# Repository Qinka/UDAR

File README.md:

# UDAR

This repo is a demo of **Ultrasound Detection And Ranging**, UDAR for short.
This demo includes a hardware design and a host software.
The hardware includes two servos, a ultrasound ranging module and FPGA IP core.
The host software will include the control program and other programs.

## Hardware

The hardware includes:

* 2-D holder
* Two servos for holder's x-axis and y-axis.
* Ultrasound ranging module(URM).
* ZigBee module(option)

The holder with two servos can change the direction of URM to $(x,y)$

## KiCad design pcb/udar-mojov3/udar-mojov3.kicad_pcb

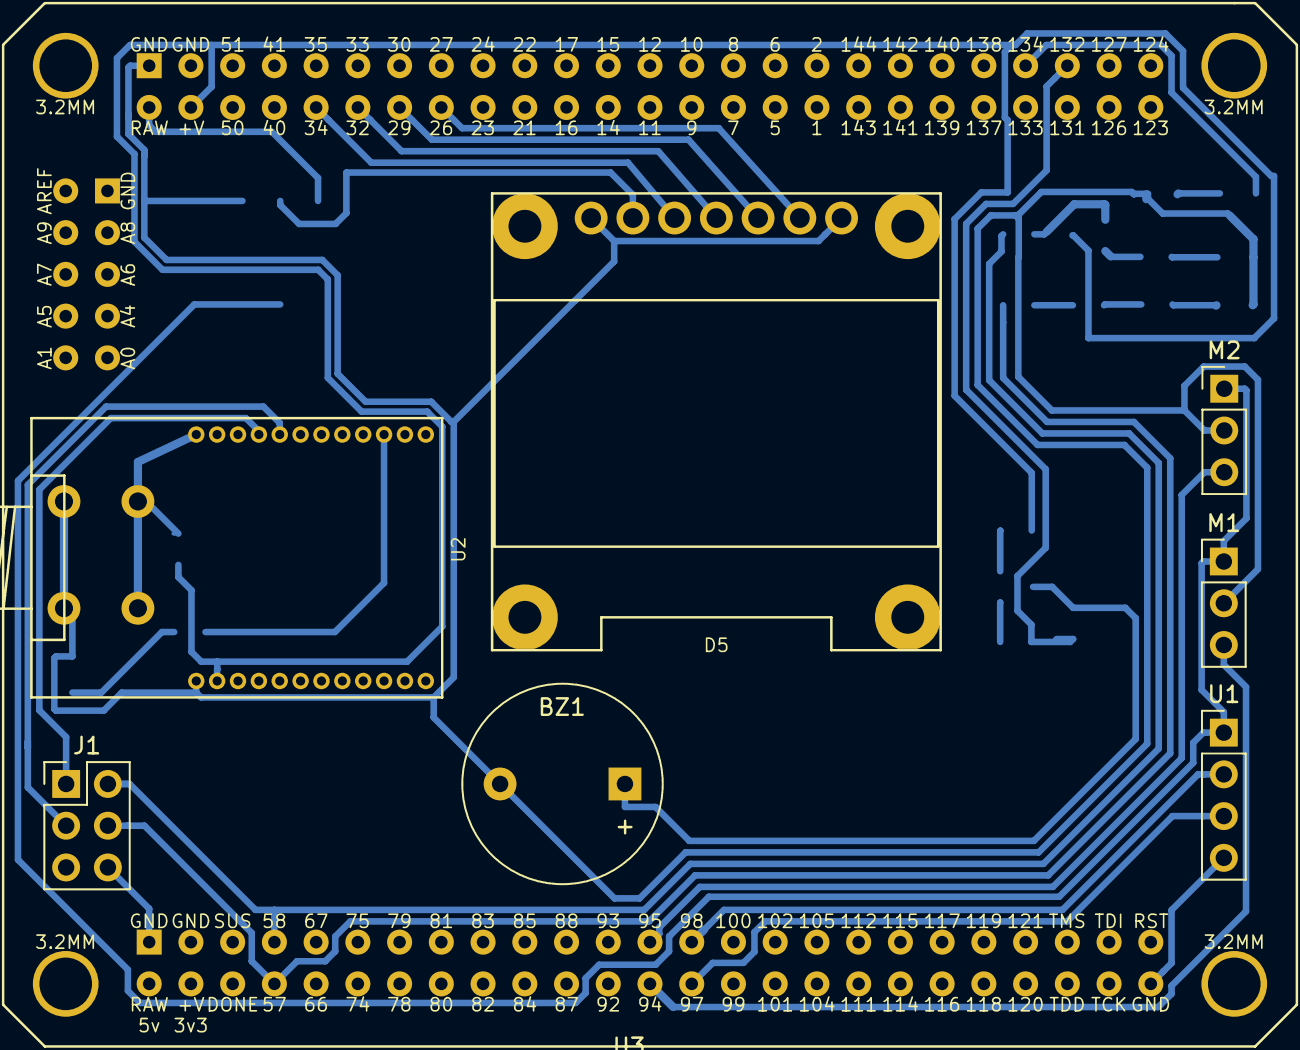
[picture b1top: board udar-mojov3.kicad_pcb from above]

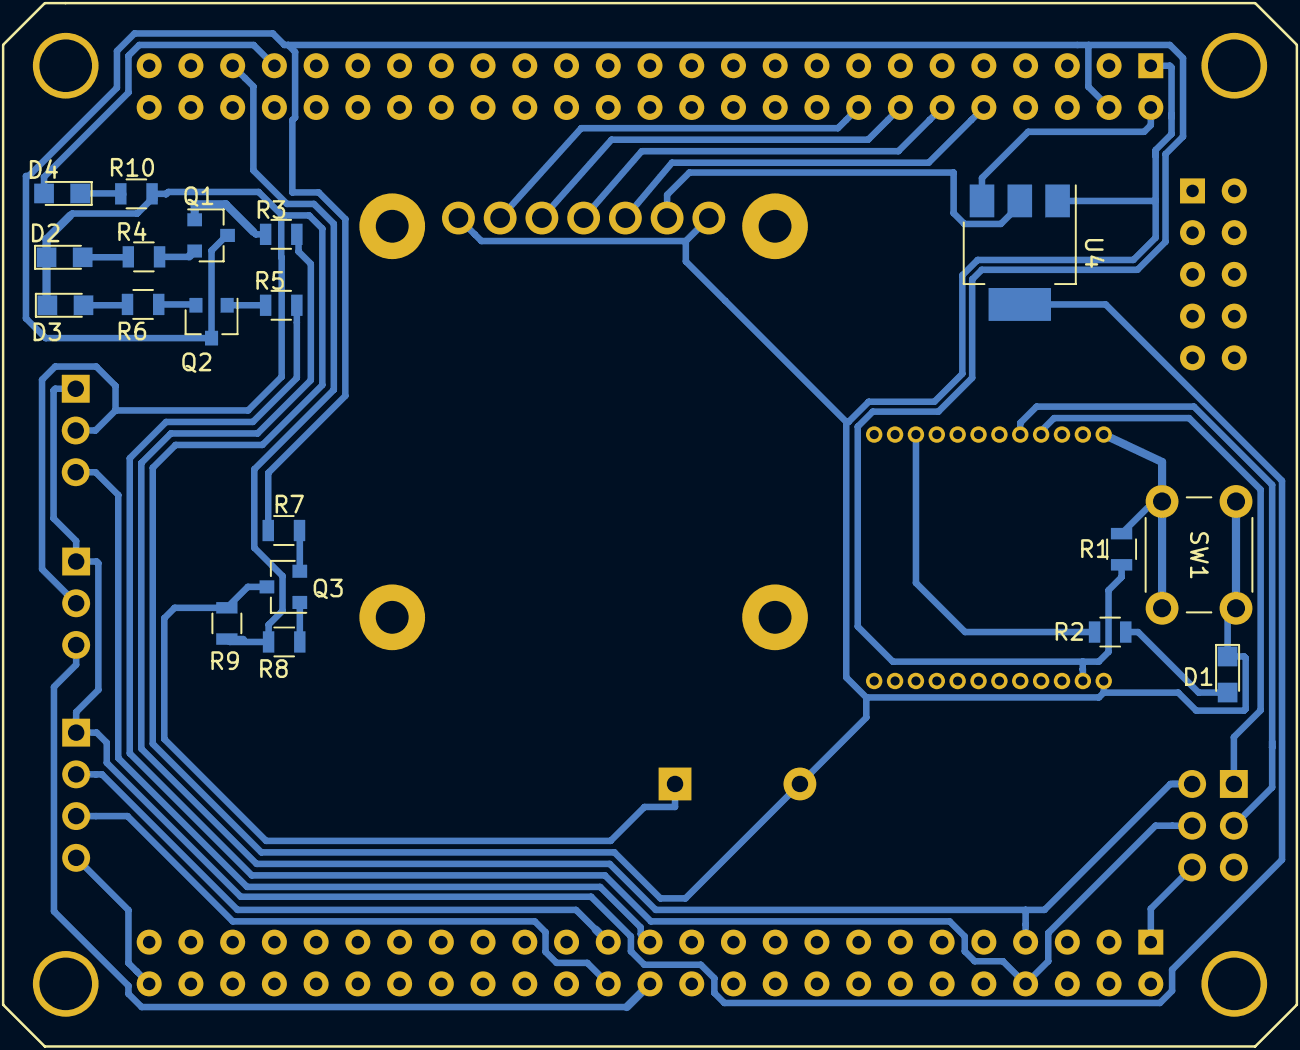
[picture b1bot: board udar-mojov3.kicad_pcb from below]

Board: 2 copper layers, 27 parts (19 on the bottom side), 31 nets.

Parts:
BZ1: Buzzer; Buzzer_12x9.5RM7.6
D1, D2, D3, D4: LED; LED_0805
D5: OLED; OLED_096_12864_SSD1306
J1: Conn_02x03_Odd_Even; Pin_Header_Straight_2x03_Pitch2.54mm
M1, M2: Motor_Servo_AirTronics; Pin_Header_Straight_1x03_Pitch2.54mm
Q1, Q2: Q_PNP_BCE; SOT-23
Q3: Q_NPN_BCE; SOT-23
R1, R2, R3, R4, R5, R6, R7, R8, R9, R10: R; R_0805
SW1: SW_Push; SW_PUSH_6mm
U1: HC-SR04; Pin_Header_Straight_1x04_Pitch2.54mm
U2: ZG-Mxx; ZG-Mxx_DIP_E
U3: Mojov3; mojov3
U4: AP1117-50; SOT-223-3_TabPin2

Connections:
+3V3: Q1.3, Q2.3, R1.1, R7.1, U2.A2, U3.+V
+5V: D5.2, M1.1, M2.1, U1.1, U4.2
/0.96 OLED/CLK: D5.3, U3.34
/0.96 OLED/DATA: D5.4, U3.32
/0.96 OLED/DC: D5.6, U3.26
/0.96 OLED/RST: D5.5, U3.29
/UART/UART_RX: J1.4, R5.2, U3.57
/UART/UART_TX: J1.2, R3.2, U3.58
/UDAR-board/Echo: U1.3, U3.97
/UDAR-board/PWM1: M1.3, U3.94
/UDAR-board/PWM2: M2.3, U3.95
/UDAR-board/Trig: U1.2, U3.98
GND: BZ1.2, D1.1, D2.1, D3.1, D5.1, D5.7, J1.6, M1.2, M2.2, R10.2, SW1.2, U1.4, U2.A1, U3.GND, U4.1
unnamed: BZ1.1, Q3.3, R9.2
unnamed: D1.2, R2.1
unnamed: D2.2, R4.2
unnamed: D3.2, R6.2
unnamed: D4.1, R10.1
unnamed: D4.2, U3.134
unnamed: J1.1, U2.B4
unnamed: J1.3, U2.B5
unnamed: Q1.1, R3.1
unnamed: Q1.2, R4.1
unnamed: Q2.1, R5.1
unnamed: Q2.2, R6.1
unnamed: Q3.1, R8.2
unnamed: Q3.2, R7.2
unnamed: R1.2, SW1.1, U2.B1
unnamed: R2.2, U2.B10
unnamed: R8.1, R9.1, U3.132
unnamed: U3.RAW, U4.3

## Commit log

2018-04-09 update add the basic circle
2018-05-07 update
    Add the basic project of Mojov3 FPGA
2018-05-07 add files; update pwm.v
    Add the there files:
    1. ctrl.v for controlling hold system
    2. pwm.v for Pulse Widh Modulation
    3. udd.v for ultrasonic rangefinder device driver
    Update the pwm.v:
    1. finish the pwm module with the example from embeddedmicro's Mojo v3's tutorial.
2018-05-11 update
    Add the pcb and sch of Mojo v3.
2018-05-11 rm the mojo v3 mods
2018-05-11 update; add mojo v3
2018-05-12 remove temp
2018-05-13 update; add;
    1. Rename the pwm.v to pwm_basic.v
    2. Add file 1602a.v for 1602A LCD
    3. Add file servo.v for servos
2018-05-13 Update; Add
    1. Update random-kicad-lib for ZG-Mxx(zigbee) modules
    2. Update 1602A
    3. Update board
    4. Add UART(with ZG-Mxx)
2018-05-18 rename
2018-05-18 update
    1. Add the trig.v and test bench
2018-05-18 Update
    1. Restruct the PCB
    2. Change 1602 to OLED(12864)
    3. Finish PCB
2018-05-20 Update
    1. Add the fq.v for frequency division.(finish)
    2. Add hscr04.v for drive HS-SR04.(in processing)
2018-05-24 update
    1. Add the timeout module for counting down.
    2. Add the servo module for controlling servo.
    3. Modified pwm.v for fix bugs.
2018-05-27 Update, and finish.
    1. Copy the serial module from mojo base project.
    2. Add the test bench for serial modules.
    3. Add ctrl.v for controlling the system.
    4. The post-place & route test is OK.
2018-05-27 update, delete
    1. Rewrite some codes
    2. Delete the udd.v(never useed)
2018-05-28 Update
    1. Update the hardware which worked well.
    2. Add the program to read from hardware (via ZigBee)
2018-05-28 Update
    1. Re-design the translation of origin data and Euclidean space
2018-06-03 Update for 0.1-alpha1
2018-06-03 Update;
2018-06-05 Update (Card-10280892 step 1)
    1. Store 1 to 5 are done
    modified: hardware_description/ctrl.v
    2. Store 1 to 5 are verified
    modified: hardware_description/test_bench/ctrl_tb.v
    3. Add the ``.ignore'' into ``.gitignore'' file.
    modified: .gitignore
2018-06-09 Fix #1
    1. Add the timeout function.
    2. There is a way needed to reset URM.(TODO)
